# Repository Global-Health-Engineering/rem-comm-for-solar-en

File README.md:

<!-- badges: start -->

<!-- badges: end -->

<h1> Development of a Remote Communications Infrastructure for an Off-Grid Energy System: Hardware, Software, and Data </h1>

<b>Contributors</b>  
- Jerun Voeten <a href="https://orcid.org/0009-0009-9822-1285">
 0009-0009-9822-1285
</a> *author, developer, maintainer*  
- Rebecca Alcock <a href="https://orcid.org/0000-0002-6884-9583">
 0000-0002-6884-9583
</a> *supervisor*  
- Jakub Tkaczuk <a href="https://orcid.org/0000-0001-7997-9423">
 0000-0001-7997-9423
</a> *supervisor, maintainer*  
- Elizabeth Tilley <a href="https://orcid.org/0000-0002-2095-9724">
 0000-0002-2095-9724
</a> *supervisor*  

<br>
<p align="middle"> 

<br><br>
It complements the openly-accessible master’s thesis, available on the<br \>  
<a href="">ETH Research Collection</a>.
</p>

# Overview
Monitoring off-grid energy systems in remote locations with unreliable communications is challenging, yet it is essential in health facilities where continuous power supports patient care. Currently, there is no simple end-to-end solution that reliably captures all relevant variables and forwards them autonomously to a site with internet access for analysis and response.

This thesis develops such a system for an off-grid health clinic in Tezhumke, northern Colombia. The design combines existing low-power sensing and long-range radio techniques with practical extensions for constrained clinical sites. In particular, robustness measures and encoding optimizations were added to improve packet delivery over Long Range (LoRa) links, and the overall architecture was engineered to run autonomously from small photovoltaic panels and local power bank storage.

Custom sensor nodes record key measurements: medical refrigerator temperature and humidity, electrical parameters of the off-grid power system, and environmental data. Measurements are transmitted over LoRa and Long Range Wide-Area Network (LoRaWAN) to a gateway, visualized on an Internet of Things (IoT) platform (ThingsBoard), and automatically archived. Alarm rules notify remote researchers and on-site staff via platform alerts, email, SMS, and visual signals when thresholds are exceeded.

In a 7-day field trial, the system achieved a packet reception rate of 97.64% over a distance of 8.5km and demonstrated stable autonomous operation. These results confirm that the system is a mature prototype ready for extended field trials and potential deployment in real-world conditions. Future work should include extended seasonal testing, long-term studies of battery aging, and improvements to the weatherproofing of individual components.

Beyond the immediate use case in Tezhumke, the system may also be applicable to other similarly affected clinics or remote sites. With further refinement, it could support predictive maintenance strategies and contribute to improved reliability of off-grid power supplies, thereby strengthening healthcare delivery in underserved regions.

# Repository
As part of this Master thesis, all developed resources have been collected and systematically documented in this public GitHub repository. The repository serves as a comprehensive reference point for future research and practical applications. It includes:

- Source code for LoRa / LoRaWAN communication,
- ThingsBoard dashboard configuration and the main payload decryption script,
- Dedicated scripts for automated data export,
- PCB layouts and electronic circuit schematics,
- All custom-designed 3D models provided in STL format,
- A complete bill of materials for all hardware components.

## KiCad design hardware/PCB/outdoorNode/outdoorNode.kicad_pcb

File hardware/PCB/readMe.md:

# `hardware/PCB`

This directory contains PCB layouts and electronic circuit schematics created with KiCad for the:
- indoor node
- outdoor node
- repeater node

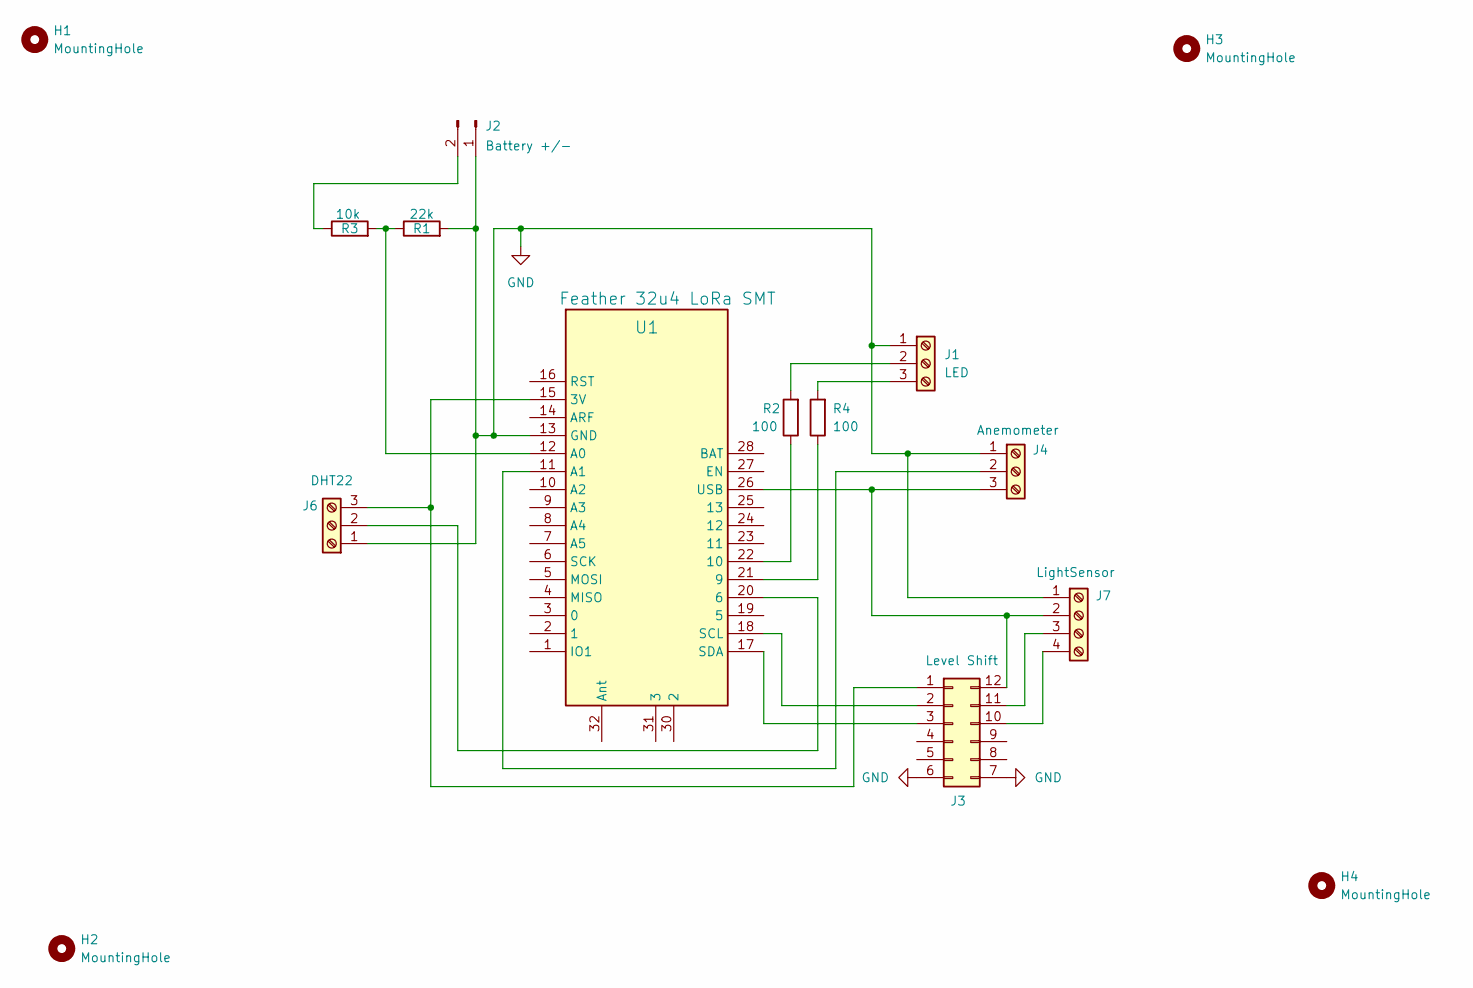
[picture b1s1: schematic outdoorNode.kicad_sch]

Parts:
H1, H2, H3, H4: MountingHole; MountingHole_4.3mm_M4
J1: LED; TerminalBlock_MaiXu_MX126-5.0-03P_1x03_P5.00mm
J2: Battery +/-; JST_PH_B2B-PH-K_1x02_P2.00mm_Vertical
J3: Level Shift; PinHeader_2x06_P2.54mm_Vertical
J4: Anemometer; TerminalBlock_MaiXu_MX126-5.0-03P_1x03_P5.00mm
J6: DHT22; TerminalBlock_MaiXu_MX126-5.0-03P_1x03_P5.00mm
J7: LightSensor; TerminalBlock_MaiXu_MX126-5.0-04P_1x04_P5.00mm
R1: 22k; R_Axial_DIN0207_L6.3mm_D2.5mm_P10.16mm_Horizontal
R2, R4: 100; R_Axial_DIN0207_L6.3mm_D2.5mm_P10.16mm_Horizontal
R3: 10k; R_Axial_DIN0207_L6.3mm_D2.5mm_P10.16mm_Horizontal
U1: Feather 32u4 LoRa SMT; mod2_Adafruit_Feather_32u4_RFM_WithMountingHoles_1

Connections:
GND: J1.1, J2.1, J3.6 (GND), J3.7 (GND), J4.1, J6.1, J7.1, R1.2, U1.13 (GND)
unnamed: J1.2, R2.2
unnamed: J1.3, R4.2
unnamed: J2.2, R3.1
unnamed: J3.2 (A1), U1.18 (SCL)
unnamed: J3.3 (A2), U1.17 (SDA)
unnamed: J3.11 (B1), J7.3
unnamed: J3.10 (B2), J7.4
unnamed: J3.12 (HV), J4.3, J7.2, U1.26 (USB)
unnamed: J3.1 (LV), J6.3, U1.15 (3V)
unnamed: J4.2, U1.11 (A1)
unnamed: J6.2, U1.20 (6)
unnamed: R4.1, U1.21 (9)
unnamed: R2.1, U1.22 (10)
unnamed: R1.1, R3.2, U1.12 (A0)

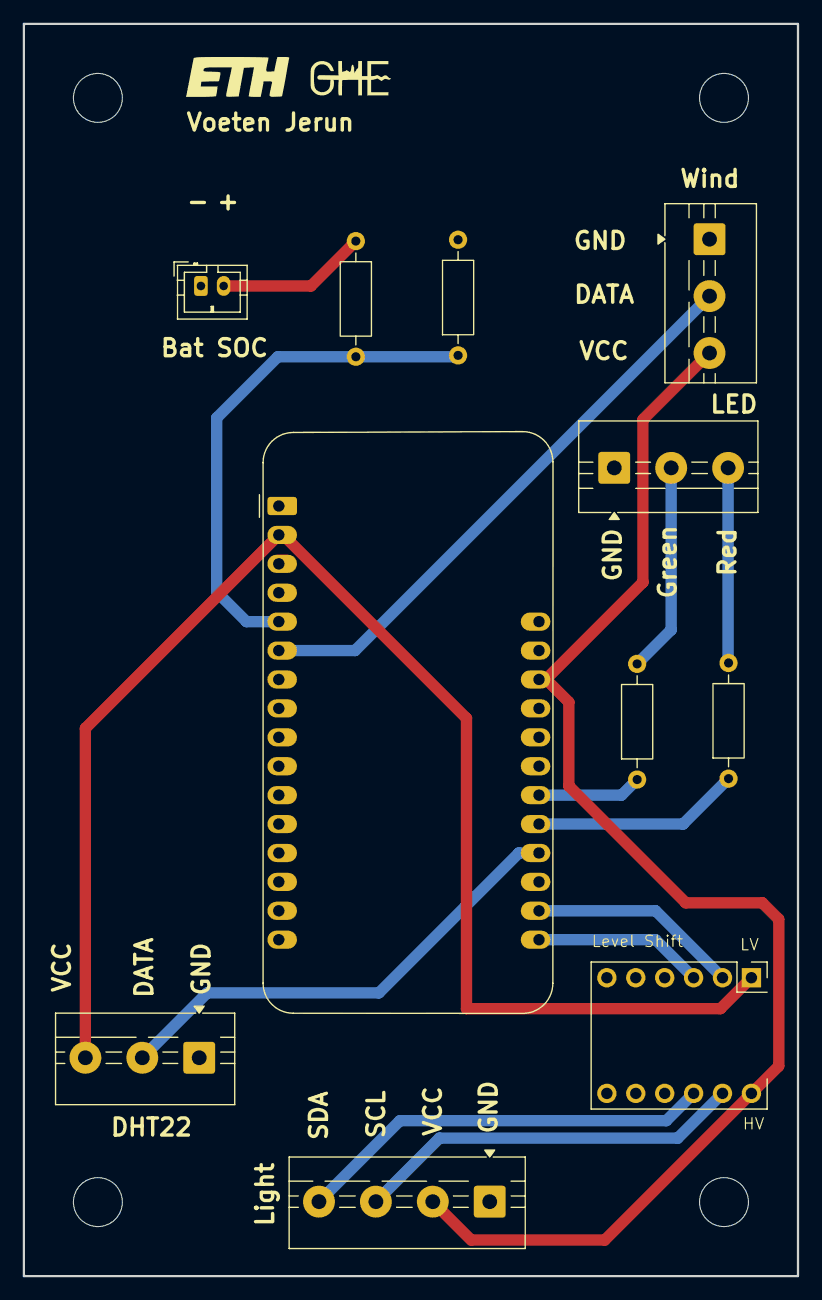
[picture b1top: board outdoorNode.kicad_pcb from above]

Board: 2 copper layers, 68.0 x 110.0 mm, 15 parts (0 on the bottom side), 15 nets.

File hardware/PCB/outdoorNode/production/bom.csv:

Designator,Footprint,Quantity,Value,LCSC Part #
J1,TerminalBlock_MaiXu_MX126-5.0-03P_1x03_P5.00mm,1,LED,
J2,JST_PH_B2B-PH-K_1x02_P2.00mm_Vertical,1,Conn_01x02_Pin,
J3,PinHeader_2x06_P2.54mm_Vertical,1,Level Shift,
J4,TerminalBlock_MaiXu_MX126-5.0-03P_1x03_P5.00mm,1,Anemometer,
J6,TerminalBlock_MaiXu_MX126-5.0-03P_1x03_P5.00mm,1,DHT22,
J7,TerminalBlock_MaiXu_MX126-5.0-04P_1x04_P5.00mm,1,LightSensor,
R1,R_Axial_DIN0207_L6.3mm_D2.5mm_P10.16mm_Horizontal,1,22k,
"R2, R4",R_Axial_DIN0207_L6.3mm_D2.5mm_P10.16mm_Horizontal,2,100,
R3,R_Axial_DIN0207_L6.3mm_D2.5mm_P10.16mm_Horizontal,1,10k,
U1,mod2_Adafruit_Feather_32u4_RFM_WithMountingHoles_1,1,Feather 32u4 LoRa SMT,

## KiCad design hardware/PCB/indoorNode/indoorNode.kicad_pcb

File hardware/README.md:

# `hardware`

This directory contains 3D designs, PCB layouts (KiCad), LoRa32u4II datasheet and a complete bill of materials for all hardware components.

# Power Bank Warning

Wires have been soldered to the + and – terminals of the power bank PCB (Solar Manager C). As a result, the manufacturer’s warranty is void, and I do not assume any responsibility in the event of issues, fire, or other incidents.
However, during the testing phase everything worked without any problems, and the functionality of the power bank did not appear to be affected.

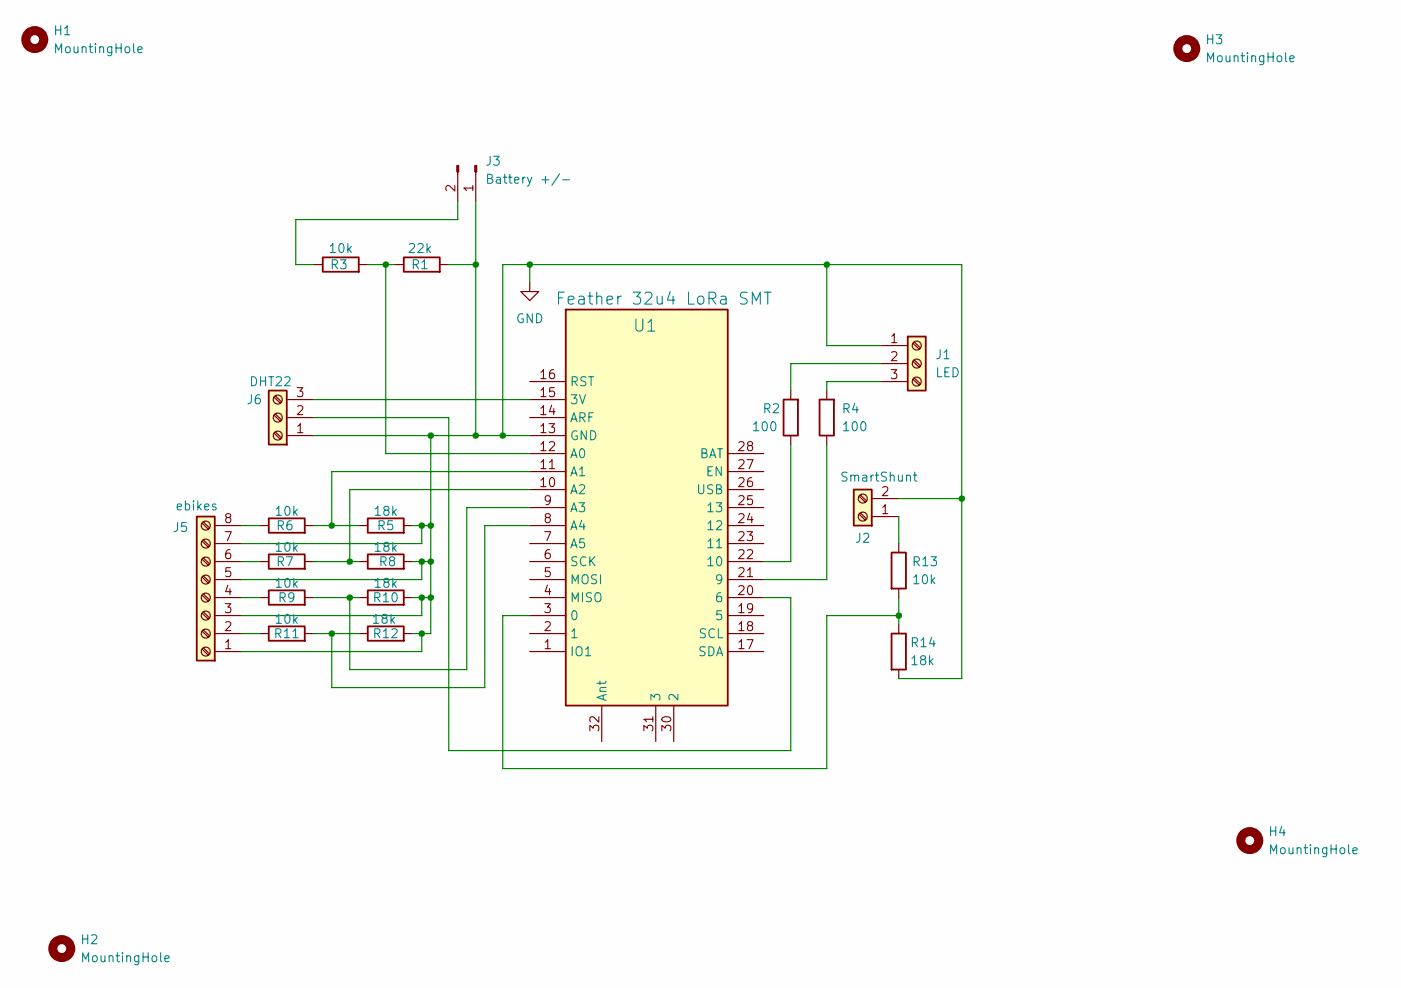
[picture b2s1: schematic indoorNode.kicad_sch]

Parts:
H1, H2, H3, H4: MountingHole; MountingHole_4.3mm_M4
J1: LED; TerminalBlock_MaiXu_MX126-5.0-03P_1x03_P5.00mm
J2: SmartShunt; TerminalBlock_MaiXu_MX126-5.0-02P_1x02_P5.00mm
J3: Battery +/-; JST_PH_B2B-PH-K_1x02_P2.00mm_Vertical
J5: ebikes; TerminalBlock_MaiXu_MX126-5.0-08P_1x08_P5.00mm
J6: DHT22; TerminalBlock_MaiXu_MX126-5.0-03P_1x03_P5.00mm
R1: 22k; R_Axial_DIN0207_L6.3mm_D2.5mm_P10.16mm_Horizontal
R2, R4: 100; R_Axial_DIN0207_L6.3mm_D2.5mm_P10.16mm_Horizontal
R3, R6, R7, R9, R11, R13: 10k; R_Axial_DIN0207_L6.3mm_D2.5mm_P10.16mm_Horizontal
R5, R8, R10, R12, R14: 18k; R_Axial_DIN0207_L6.3mm_D2.5mm_P10.16mm_Horizontal
U1: Feather 32u4 LoRa SMT; mod2_Adafruit_Feather_32u4_RFM_WithMountingHoles_1

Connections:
GND: J1.1, J2.2, J3.1, J5.1, J5.3, J5.5, J5.7, J6.1, R1.2, R5.2, R8.2, R10.2, R12.2, R14.2, U1.13 (GND)
unnamed: J1.2, R2.2
unnamed: J1.3, R4.2
unnamed: J2.1, R13.1
unnamed: J3.2, R3.1
unnamed: J5.2, R11.1
unnamed: J5.4, R9.1
unnamed: J5.6, R7.1
unnamed: J5.8, R6.1
unnamed: J6.2, U1.20 (6)
unnamed: J6.3, U1.15 (3V)
unnamed: R13.2, R14.1, U1.3 (0)
unnamed: R4.1, U1.21 (9)
unnamed: R2.1, U1.22 (10)
unnamed: R1.1, R3.2, U1.12 (A0)
unnamed: R5.1, R6.2, U1.11 (A1)
unnamed: R7.2, R8.1, U1.10 (A2)
unnamed: R9.2, R10.1, U1.9 (A3)
unnamed: R11.2, R12.1, U1.8 (A4)

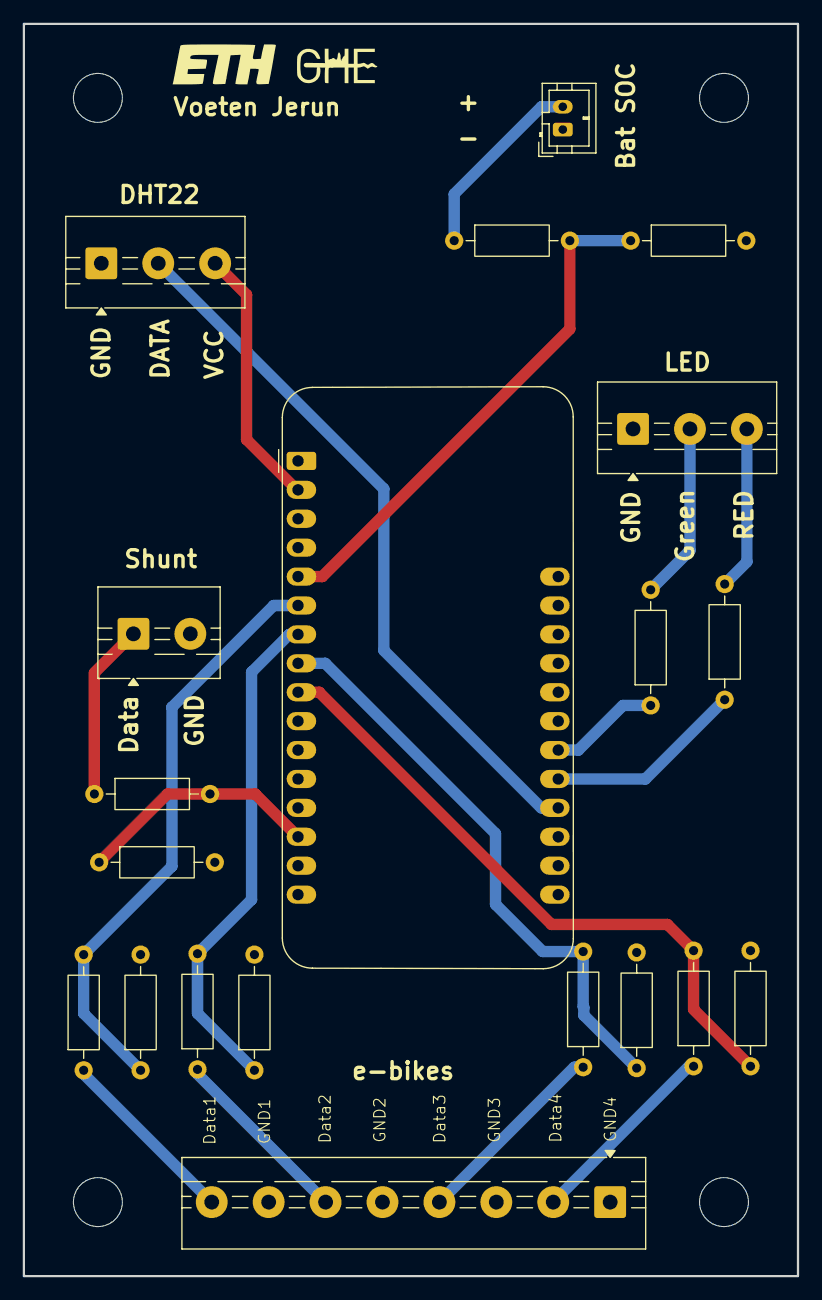
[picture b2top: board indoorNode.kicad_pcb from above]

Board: 2 copper layers, 68.0 x 110.0 mm, 24 parts (0 on the bottom side), 19 nets.

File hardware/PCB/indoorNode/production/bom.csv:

Designator,Footprint,Quantity,Value,LCSC Part #
J1,TerminalBlock_MaiXu_MX126-5.0-03P_1x03_P5.00mm,1,LED,
J2,TerminalBlock_MaiXu_MX126-5.0-02P_1x02_P5.00mm,1,SmartShunt,
J3,JST_PH_B2B-PH-K_1x02_P2.00mm_Vertical,1,Battery +/-,
J5,TerminalBlock_MaiXu_MX126-5.0-08P_1x08_P5.00mm,1,ebikes,
J6,TerminalBlock_MaiXu_MX126-5.0-03P_1x03_P5.00mm,1,DHT22,
R1,R_Axial_DIN0207_L6.3mm_D2.5mm_P10.16mm_Horizontal,1,22k,
"R10, R12, R14, R5, R8",R_Axial_DIN0207_L6.3mm_D2.5mm_P10.16mm_Horizontal,5,18k,
"R11, R13, R3, R6, R7, R9",R_Axial_DIN0207_L6.3mm_D2.5mm_P10.16mm_Horizontal,6,10k,
"R2, R4",R_Axial_DIN0207_L6.3mm_D2.5mm_P10.16mm_Horizontal,2,100,
U1,mod2_Adafruit_Feather_32u4_RFM_WithMountingHoles_1,1,Feather 32u4 LoRa SMT,

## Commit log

2025-09-09 make repo structure
2025-09-09 update orcid
2025-09-29 change license
2025-09-29 update description
2025-09-29 add fig description
2025-09-29 add doi
2025-09-29 update readmes

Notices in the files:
README.md:
License: Apache 2.0
